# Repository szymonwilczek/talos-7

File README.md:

# ⚡ Talos 7
### The Ultimate Open-Source SudoPad 

<div align="center">
  
  <br/>

</div>

---

## 📸 Preview

<table>
  <tr>
    <td width="50%" align="center">
      
    </td>
    <td width="50%" align="center">
      
    </td>
  </tr>
  <tr>
    <td colspan="2" align="center">
      
    </td>
  </tr>
</table>

<div align="center">
  <video src="https://github.com/user-attachments/assets/fb88e3e2-818f-48c2-9b6d-56c365594454" controls></video>
</div>

---

## 📖 Overview

**Talos 7** is not just a keypad; it's a hardware productivity platform. I've name this functionality as SudoPad. Unlike traditional macro pads that rely on heavy background software (like Synapse or iCUE), **Talos 7 runs everything on the device itself**.

Once configured via the web interface, you can plug it into **any computer** (Windows, macOS, Linux), and it will work instantly. No drivers. No background agents. Just pure hardware emulation.

### Why Talos?
* **Hybrid Device:** Simultaneously acts as a Keyboard, Mouse, MIDI Controller, and Serial Device.
* **OLED Dashboard:** A 128x64 pixel display gives you real-time feedback on layers and actions.
* **Web Configurator:** Modify your layout directly in Chrome/Edge using Web Serial API.
* **Hephaestus CI/CD:** Automated cloud builds ensure you always have the latest firmware.

---

## 🛠️ Hardware Architecture

Talos 7 is built on the accessible and powerful **Raspberry Pi Pico (RP2040)**.

### Bill of Materials (BOM)
* 1x **Raspberry Pi Pico**
* 7x **Mechanical Switches** (MX standard)
* 7x **Keycaps** (MX standard)
* 1x **SSD1306 OLED Display** (0.96", SPI Interface)
* 7x **LEDs** (0805, red)
* 10x **Resistors** (220R or 47R if you prefer dimmer light)
* 1x **RGB LED** (LTST-G563ZEGBW or FYLS-5050NRGBC)
* 1x **Micro-USB Data Cable**

### Wiring Diagram (Pinout)

See [Talos Schema](assets/board/talos_schema.pdf) for more information.

## 🚀 Setup & Installation

### 1. Flash the Firmware
You don't need to compile anything manually.
1.  Go to [**Releases**](https://github.com/szymonwilczek/talos-7/releases).
2.  Download the latest `talos7.uf2`.
3.  Hold the **BOOTSEL** button on your Pico while plugging it into USB.
4.  A drive named `RPI-RP2` will appear. Drag and drop the `.uf2` file there.
5.  The device will reboot. You should see the Talos Logo on the OLED.

### 2. Configure via Web
1.  Open the **[Talos Configurator](https://talos-7.vercel.app)** in a Chromium-based browser (Chrome, Edge, Opera).
2.  Click **Connect Device** and select *Talos 7*.
3.  **Customize** your layers and buttons.
4.  Click **Save Changes** to flash your config to the onboard memory.

---

## 🎛️ Macro Dictionary

Talos 7 supports **8 distinct action types** (for now, if you have something in mind, be welcome to propose). Here is a deep dive into each capabilities.

### 1. ⌨️ Key Press
Simulates a standard keyboard press.
* **Parameters:** Keycode (A-Z, F1-F12, etc.).
* **Use Case:** Muting Discord (`F13`), Screenshot (`PrintScreen`), Game abilities (`Q`, `W`, `E`).

### 2. ⛓️ Key Sequence
Executes a precise combination of up to 3 keys pressed simultaneously or sequentially.
* **Parameters:** List of keys + Modifiers (Ctrl, Alt, Shift, GUI).
* **Use Case:** `Ctrl` + `Shift` + `Esc` (Task Manager), `Win` + `Shift` + `S` (Snipping Tool).

### 3. 🔡 Text String
Types a text snippet automatically.
* **Parameters:** Text content (up to 32 chars).
* **Behavior:** Works like a super-fast typist. Supports basic Unicode.
* **Use Case:** Email signatures, Git commands (`git push origin main`), etc.

### 4. 🔄 Layer Toggle
Switches the active layer of the device.
* **Parameters:** Target Layer (Automatic Cycle).
* **Behavior:** Pressing this creates a loop: `Layer 1` → `Layer 2` → `Layer 3` → `Layer 4` → `Layer 1`.
* **Visuals:** The OLED instantly updates to show the new layer's name and icon.

### 5. 🖱️ Mouse Control
Takes hardware control of the mouse cursor.
* **Sub-types:**
    * **Move:** X/Y coordinates (relative). Great for AFK scripts.
    * **Click:** Left, Right, or Middle button (with Hold support).
    * **Wheel:** Scroll Up/Down.
* **Use Case:** "Cookie Clicker" macros, in-game AFK preventions, preventing screen lock.

### 6. 📜 Script Engine (Power User)
The most powerful feature. Talos acts as a "BadUSB" device to inject and execute complex scripts on the host machine.
* **Platform Awareness:** You can define separate scripts for Windows, Linux, and macOS on the same button.
* **Workflow:**
    1.  Talos opens a terminal using a shortcut (e.g., `Win+R` or `Ctrl+Alt+T` - those are just default, you can provide your own sequence if you have it).
    2.  It types a temporary script file to `/tmp` or `%TEMP%`.
    3.  It executes the file and deletes it immediately.
* **Use Case:** `docker-compose up -d`, SSH into a server, batch rename files, organize desktop.

### 7. 🎹 MIDI Note (Studio Mode)
Sends a MIDI Note On/Off signal via USB MIDI class.
* **Parameters:** Note (0-127), Velocity (0-127), Channel (1-16).
* **Why MIDI?** Unlike keyboard shortcuts, MIDI messages **never conflict** with typing and work even when the target app is in the background.
* **Integration:**
    * **OBS:** Use `obs-midi` plugin to switch scenes or toggle sources.
    * **DAWs:** Map to drum pads in FL Studio / Ableton.

### 8. 🎚️ MIDI Control Change (CC)
Sends a generic MIDI value (Potentiometer/Fader simulation).
* **Parameters:** CC Number (0-119), Value (0-127), Channel (1-16).
* **Use Case:**
    * **Lightroom:** Set Exposure to +1.0.
    * **Premiere Pro:** Set Timeline Zoom level.
    * **Windows Volume:** Use middleware (e.g., MidiKey2Key) to map CC to system volume.

### 9. 🕹️ Atari Breakout Game
A pleasant *Break* during work

---

## 🤖 DevOps: Hephaestus

This repository is managed by an automated github workflow named **Hephaestus**.

### Automated Versioning
I use **Semantic Versioning**. Hephaestus parses every commit message:
* `fix: ...` ➜ Bumps **Patch** (1.0.0 ➜ 1.0.1)
* `feat: ...` ➜ Bumps **Minor** (1.0.1 ➜ 1.1.0)
* `feat!: ...` ➜ Bumps **Major** (1.1.0 ➜ 2.0.0)

### Continuous Delivery
On every valid push to `main`:
1.  Hephaestus spins up a cloud environment with the **ARM GCC Toolchain**.
2.  It checks out the official **Pico SDK**.
3.  It compiles the firmware (`talos7.uf2`).
4.  It creates a **GitHub Release** with the new version and changelog.

---

## 🔧 Troubleshooting

### Device not connecting in browser?
* **Windows:** Ensure you are not blocking USB devices via Group Policy. No drivers needed.
* **Linux:** If you are unable to connect to the device via the web configurator on Linux (receiving `NetworkError: Failed to execute open on SerialPort`), you need to configure `udev` rules to allow non-root access to the Raspberry Pi Pico.

1. **Create a new udev rule file:**
   ```bash
   sudo nano /etc/udev/rules.d/99-talos.rules
   ```

2. **Add the following content**: This grants r/w permission to the device (Vendor ID 0x2e8a is RPi Pico):

```text
SUBSYSTEMS=="usb", ATTRS{idVendor}=="2e8a", MODE="0666"
KERNEL=="ttyACM*", ATTRS{idVendor}=="2e8a", MODE="0666"
```

3. Reload the rules and reconnect:

```bash
sudo udevadm control --reload-rules # reload
sudo udevadm trigger # apply changes
```

**Note for Fedora/RHEL users**: If connection issues persist, ModemManager might be interfering with the serial port. You can temporarily stop it with: `sudo systemctl stop ModemManager`

* **Browser:** Use Chrome, Edge, or Opera. Firefox/Safari do not support Web Serial yet.

### Firmware update failed?
If you "bricked" the configuration or the device is unresponsive:
1.  Unplug the device.
2.  Hold the physical **BOOTSEL** button on the Pico.
3.  Plug it in.
4.  Flash the `.uf2` again. This factory resets the core logic.

---

## 📄 License & Credits

* **Core Logic:** Szymon Wilczek
* **3D Case**: Kacper Kil, thanks a lot again!
* **Project Link:** [github.com/szymonwilczek/talos-7](https://github.com/szymonwilczek/talos-7)
* **License:** [MIT License](./LICENSE.md)

Thanks for interest in my project!

Built with ❤️ using **Raspberry Pi Pico SDK** and **TinyUSB**.

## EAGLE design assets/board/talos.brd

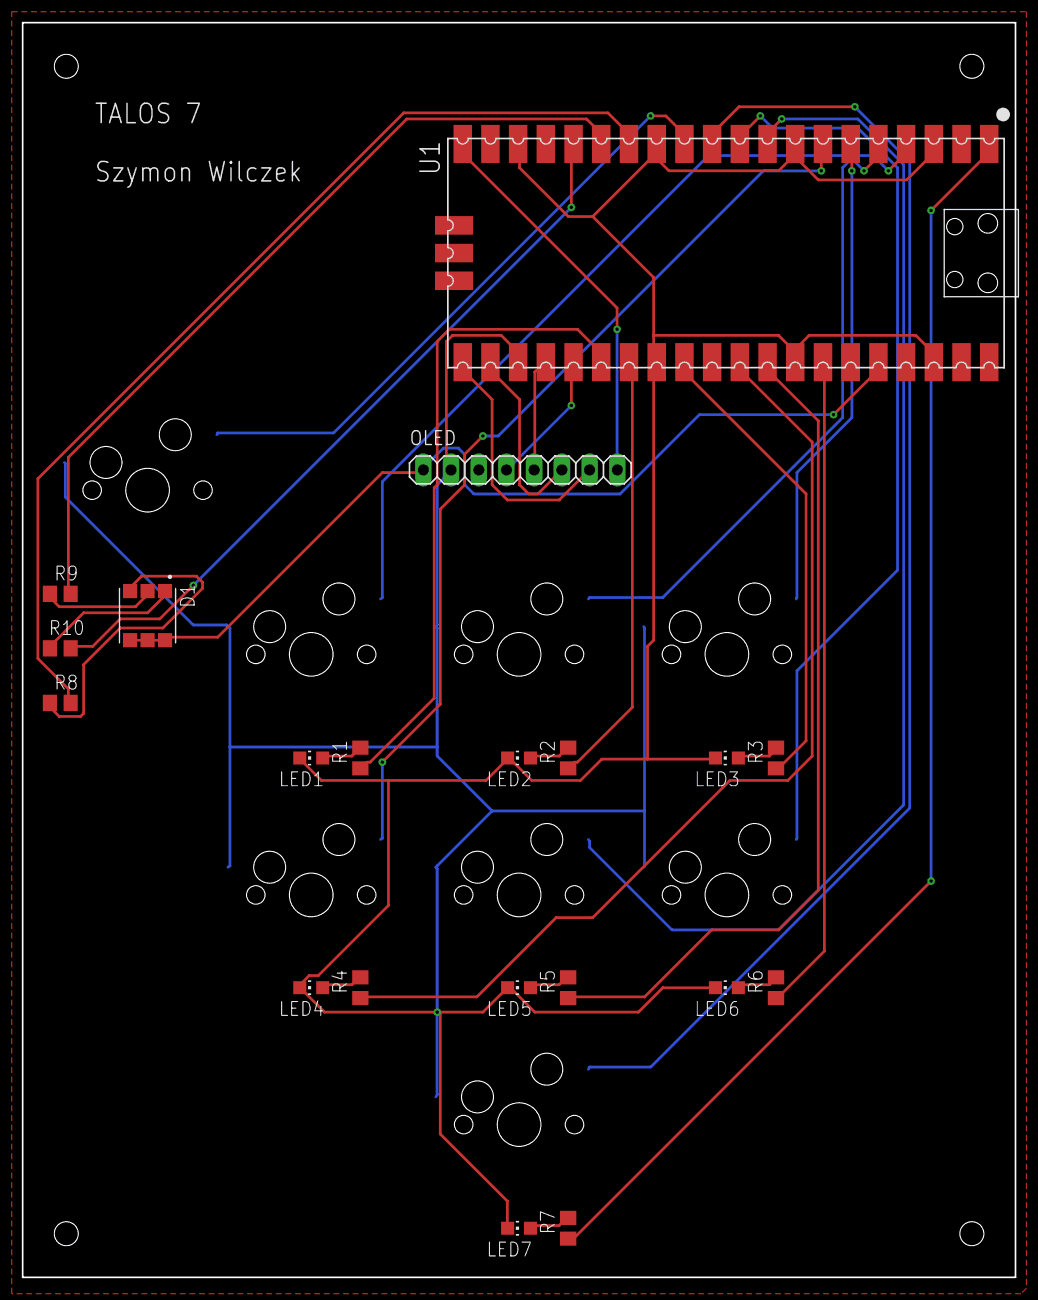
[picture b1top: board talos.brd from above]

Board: 2 copper layers, 91.0 x 115.0 mm, 28 parts (0 on the bottom side), 35 nets.

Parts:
D1: LTST-G563ZEGBW; LED_LTST-G563ZEGBW
LED1, LED2, LED3, LED4, LED5, LED6, LED7: BLUE; CHIP-LED0805
OLED: SSD106_SPI; 1X08
R1, R2, R3, R4, R5, R6, R7, R9, R10: 220R; R0805
R8: 330R; R0805
SW1, SW2, SW3, SW4, SW5, SW6, SW7, SW8: KAILH_SWITCH_SOCKET; SWITCH_SOCKET
U1: RASPBERRY_PICOSMD; PICO-PKG-SMD

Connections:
BTN1: SW1.1, U1.P$4
BTN2: SW2.1, U1.P$5
BTN3: SW3.1, U1.P$6
BTN4: SW4.1, U1.P$7
BTN5: SW5.1, U1.P$9
BTN6: SW6.1, U1.P$10
BTN7: SW7.1, U1.P$11
BTN_OS: SW8.1, U1.P$12
GND: LED1.C, LED2.C, LED3.C, LED4.C, LED5.C, LED6.C, LED7.C, OLED.2, SW1.2, SW2.2, SW3.2, SW4.2, SW5.2, SW6.2, SW7.2, SW8.2, U1.P$3, U1.P$8, U1.P$13, U1.P$18, U1.P$23, U1.P$28, U1.P$33, U1.P$38
LED1: R1.1, U1.P$26
LED2: R2.1, U1.P$27
LED3: R3.1, U1.P$29
LED4: R4.1, U1.P$31
LED5: R5.1, U1.P$32
LED6: R6.1, U1.P$34
LED7: R7.1, U1.P$1
LED_B: R10.2, U1.P$16
LED_G: R9.2, U1.P$15
LED_R: R8.2, U1.P$14
unnamed: LED1.A, R1.2
unnamed: LED2.A, R2.2
unnamed: LED3.A, R3.2
unnamed: LED4.A, R4.2
unnamed: LED5.A, R5.2
unnamed: LED6.A, R6.2
unnamed: D1.3, R8.1
unnamed: LED7.A, R7.2
unnamed: D1.1, R10.1
unnamed: D1.2, R9.1
OLED_CLK: OLED.5, U1.P$24
OLED_CS: OLED.6, U1.P$22
OLED_DC: OLED.7, U1.P$21
OLED_DIN: OLED.4, U1.P$25
OLED_RES: OLED.8, U1.P$20
VCC_OUT: D1.4, D1.5, D1.6, OLED.1, U1.P$36

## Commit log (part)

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2025-11-15 feat: ignoring build directory
2025-11-15 feat: defined pin definitions for pi pico
2025-11-15 feat: mocking hardware for now
    i dont have any components yet, still waiting
2025-11-15 feat: defined cdc protocol header
2025-11-15 feat: implemented mocking hardware for now
    still dont have any components
2025-11-15 feat: main file for firmware configuration for pi pico
2025-11-15 feat: ingoring pico-sdk in git commits
2025-11-15 feat: components for macro configuration (web-interface)
2025-11-15 feat: utils for comparing config (web-interface)
2025-11-15 feat: main serial service for whole pico operations handling
2025-11-15 feat: emojis for layers
2025-11-15 feat: handling macro/layers emojis on frontend site
2025-11-15 feat: better visualisation of project board layout on web interface
2025-11-15 feat: formatting improvements on web-interface
2025-11-16 feat: scripts handling (custom shell/bash/...etc.)
2025-11-16 feat: animating saving progress & success/error alert
2025-11-18 feat: implemented key sequences for macros
2025-11-18 feat: test script for scripting macros
2025-11-18 feat: implemented key sequences in button edit
2025-11-18 feat: implemented new commands into serial service
    new commands for key sequences macros.
    Also fixed sending scripts: previously there was usage of scriptContent.length, not script bytes.
2025-11-18 feat: implemented logs for hardware debugging
2025-11-18 feat: implemented logging function in cdc protocol
2025-11-18 feat: implemented macro executor for firmware
2025-11-18 fix: proper oled attributes for mocking hardware
2025-11-18 feat: emojis on oled display handled by firmware
2025-11-18 fix: missing import
2025-11-18 feat: specified new emoji format in web interface
2025-11-19 feat: displaying special screen when pending changes
2025-11-19 feat: 3 new emojis
2025-11-19 fix: updated default layer emojis to indexes instead of emoticons
2025-11-19 feat: new font for oled display (web interface)
2025-11-19 feat: new OLEDDisplay look (immersive) (web interface)
2025-11-19 feat: new limiters for sequence and button name
2025-11-19 fix: typo
2025-11-19 fix: proper parsing emoji for key sequence
2025-11-19 feat: macro executing for text_strings
    supporting ascii and unicode characters
2025-11-19 fix: waiting for tud HID to be ready after finishing typing
2025-11-19 feat: validating for only one layer toggle on layer
2025-11-20 fix: sending full script from firmware to web interface
2025-11-20 fix: displaying sequences on oled display (firmware)
2025-11-21 feat: preventing oled burnout by settings afk timeout
2025-11-21 feat: waking up screen when plugged in into interface
2025-11-21 feat: fast typing on key pressing
2025-11-21 fix: mouse descriptor for usb
2025-11-21 feat: smoothing out mouse move process
2025-11-21 feat: centering layer & button name for oled display (WI)
2025-11-21 fix: proper assembling terminal shortcut for scripts
    closes #8
2025-11-21 feat: excluded font from hardware interface
2025-11-21 feat: oled_display in targets
2025-11-22 feat: excluded logic from cdc_protocol to separate handlers
2025-11-22 feat: excluded logic from executor single file to separate handlers
2025-11-23 feat: boot up logo for oled display (firmware)
2025-11-23 fix: preview badge in oled display (web interface)
2025-11-23 feat: usb descriptors registering with proper author and project name
2025-11-23 feat: included firmware version before sending config
2025-11-23 chore(firmware): Hephaestus forged patch version bump [skip ci]
2025-11-23 fix: assets graphic comments in english
2025-11-23 feat: MIDI notes functionality
2025-11-23 feat: MIDI CC funcionality
2025-11-23 fix: oled display (F/WI) info about new MIDI Notes/CC
2025-11-23 chore(firmware): Hephaestus forged v1.3.1 [skip ci]
2025-11-23 fix: README updates
2025-11-24 chore(firmware): Hephaestus forged v1.4.0 [skip ci]
2025-11-24 feat!: buttons made on interrupts, not sync waiting
2025-11-24 feat: divided configurator into separate components
2025-11-24 feat: divided oled into separate components
2025-11-24 fix: deleted old pcb visualization component
2025-11-24 feat: installed types for serial port
2025-11-25 fix: usb descriptors for windows recognition (as well with other distros)
2025-11-25 Revert "fix: usb descriptors for windows recognition (as well with other distros)"
    This reverts commit 27167b515c4ee1fffe68ba926260e4a751b77a07.
2025-11-25 fix: direct values of descriptors for windows os
2025-11-25 fix: yet again another fix for windows descriptors
2025-11-25 fix: changed usb_pid specifically for windows os
2025-11-25 fix: added IAD protocol to config total len
2025-11-25 fix: forgotten definitions for IAD protocol
2025-11-25 reverted to original descriptors configuration
    i fucked something up, even linux wasn't working.
2025-11-25 chore(firmware): Hephaestus forged v2.0.0 [skip ci]
2025-11-25 fix: missing paragraph for BROWSER_NOT_SUPPORTED error
2025-11-25 Add thank you note to README
    Added a thank you note for project interest.
2025-11-26 Revise BOM with additional details and clarifications
    Updated Bill of Materials with personal notes on components.
2025-11-26 chore(firmware): Hephaestus forged v2.1.0 [skip ci]
2025-11-27 fix: proper windows unicode recognition and typing
2025-11-27 feat: possibility of changing platform via external button
    Closes #6 and closes #9
2025-11-27 feat: rgb led os indicator
2025-11-28 chore(firmware): Hephaestus forged v2.4.0 [skip ci]
2025-11-28 feat: electron wrapper for Talos configurator
2025-11-28 feat: electron release push
2025-11-30 chore(firmware): Hephaestus forged v2.4.1 [skip ci]
2025-12-01 fix: matrix rain oled screen saver
2025-12-01 feat: new graphics for screen saver animations
2025-12-01 feat: screen saver manager for managing animations
2025-12-14 fix: prevent buffer overflow in text preview
    The size of the safe_preview buffer has been increased from 16 to 20 bytes, and the
    unsafe strcat() function has been replaced with strncat() with an explicit size limit.
    This prevents a potential buffer overflow when displaying a preview of the macro text
    on the OLED screen when the text contains Unicode characters converted to ‘?’.
    Changed files:
    - firmware/src/oled/oled_display.c
2025-12-14 fix: add error handling to serial disconnect
    Robust error handling has been added to the disconnect() function:
    - Each operation (reader, writer, port) is now wrapped in a try-catch block
    - Incorrect await on the synchronous releaseLock() method has been removed
    - .catch(() => {}) has been added to reader.cancel() to catch errors before releaseLock
    This prevents the application from crashing when:
    - The device was physically disconnected before calling disconnect
2025-12-14 fix: remove duplicate boot log messages
    Duplicate logs in the print_boot_message() function have been removed.
    Previously, information about buttons, LEDs, OLEDs, and layers was printed twice each time the device was started, which cluttered
    the serial console output.
    Changed files:
    - firmware/src/main.c
2025-12-14 fix: increase response format buffer size
    The buffer size in cdc_send_response_fmt() has been increased from 256 to 512 bytes.
    The previous size could be insufficient when sending configurations containing long macro names, text strings, or other data, which led
    to truncated responses and potential data loss when reading the configuration.
    Changed files:
    - firmware/src/cdc/cdc_transport.c
2025-12-14 fix: add buffer size limit to prevent memory leak in readLine
    A buffer size limit (64KB) has been added to the readLine() function.
    If data arrives without a newline character, the buffer could grow indefinitely, leading to a memory leak. Now, when the buffer exceeds MAX_BUFFER_SIZE:
    - The buffer is cleared
    - An error is thrown: “Buffer overflow - no newline received”
    This prevents memory problems with incorrect data streams from the device.
    Changed files:
2025-12-14 fix: remove duplicate function declaration
    Removed duplicate declaration of the config_get_current_layer() function in the macro_config.h header file.
    The function was declared twice (lines 88 and 90). The C compiler accepts repeated declarations, but this is unnecessary and clutters the code.
    Changed files:
    - firmware/include/macro_config.h
2025-12-14 fix: add layer index validation in display function
    Added validation of the layer parameter at the beginning of the oled_display_layer_info() function.
    If layer >= MAX_LAYERS:
    - The message “Invalid layer!” is displayed on the OLED
    - The function returns without attempting to access the array
    This prevents out-of-bounds access with an invalid layer index, which could lead to undefined behavior or device crash.
    Changed files:
2025-12-14 fix: prevent script data from being parsed as commands
    Updated files:
    - firmware/include/cdc/cdc_transport.h
    - firmware/src/cdc/cdc_transport.c
    - firmware/src/cdc/cdc_dispatcher.c
2025-12-14 chore(firmware): Hephaestus forged v2.6.0 [skip ci]
2025-12-14 feat: main tests configuration
2025-12-14 feat: unity framework for unit tests
2025-12-14 feat: unit tests for midi actions
2025-12-14 feat: unit tests for crc32, flash storage
2025-12-14 feat: complex tests for macro_config
2026-01-18 fix: updated OS colors
    By accident I've destroyed one of the diode pads during soldering (the red one).
    I needed to come up with a truly engineered solution - instead of using the red color, I'm using single colors and their combination. I'm satisfied by now in that solution.
2026-01-21 fix(firmware): flush rx buffer before script reception
    This commit fixes a synchronization issue where the SET_MACRO_SCRIPT command header was being incorrectly read as part of the script content.
    By flushing the RX buffer before sending the READY signal and clearing the script memory, we ensure a clean state for script reception.
2026-01-21 feat(web): update oled slider step to 10s
    This change updates the OLED timeout slider step from 30s to 10s, allowing users to select more granular timeout values like 10s, 20s, etc.
2026-01-21 fix(firmware): increase typing delay to 5ms for reliability
    Increased the delay between keystrokes in exec_text.c from 2ms to 5ms. This prevents characters from being dropped by the host OS (e.g., 'cat -d' error) during rapid text injection.
2026-01-21 feat(web): send script metadata and flush serial buffer
    Updated web interface to include macro name and emoji in 'SET_MACRO_SCRIPT' command. Implemented 'flush()' in SerialTransport and added calls to flush the read buffer before critical operations (save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
2026-01-22 feat(firmware): add configurable Atari Breakout easter egg
    Implemented Atari Breakout game logic in a new easter_egg module.
    Added MACRO_TYPE_GAME (10) to macro_config.h.
    Updated macro_executor to launch the game when configured.
    The game includes paddle control, ball physics, brick destruction, and watchdog feeding.
2026-01-22 chore(firmware): Hephaestus forged v2.8.0 [skip ci]
2026-01-22 docs: fix position of video preview
2026-01-22 docs: fix video for atari preview
2026-01-22 docs: update README formatting
2026-01-23 feat: sorted out project dir structure for submission
2026-01-23 feat: bin files for device programming
2026-01-23 feat: readme and changelog
2026-01-23 fix: changelog in markdown format
2026-01-23 feat: add documentation in zip file
